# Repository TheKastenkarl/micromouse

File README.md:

# Micromouse: Designing an Educational Racing - Robot from Scratch [TUM IN2106/IN4235]

A practical course at TU Munich to build a micromouse robot from scratch, led by [Dr. Ph.D. Alexander Lenz](https://www.ce.cit.tum.de/air/people/dr-alexander-lenz/). This repository serves as a collection of code and ressources during our group work of SS22. See the official [course description](https://campus.tum.de/tumonline/wbLv.wbShowLVDetail?pStpSpNr=950367380&pSpracheNr=2) for further information.

Content overview:
- `src/`: Source and header files for the programming of a [Microchip dsPIC33FJ64MC804](https://www.microchip.com/en-us/product/dsPIC33FJ64MC804) microcontroller using the [MPLAB X IDE](https://www.microchip.com/en-us/tools-resources/develop/mplab-x-ide) and the [MPLAB XC16 Compiler](https://www.microchip.com/en-us/tools-resources/develop/mplab-xc-compilers).
- `pcb/`: Schematics and board layout designed in [Autodesk Eagle](https://www.autodesk.com/products/eagle/overview?term=1-YEAR&tab=subscription).
- `cad/`: 3D printed CAD parts including sensor and motor mountings.

## PCB

List of external Eagle libraries:

| Name  | Usage |
|-------|-------|
| [microchip-dspic33fjxxmc](http://eagle.autodesk.com/eagle/libraries?utf8=%E2%9C%93&q%5Btitle_or_author_or_description_cont%5D=dsPIC33FJ64MC&button=) | Microcontroller DSPIC33FJ64MC804 |
| [Eagle_WCAP-ATG5 (rev21a).lbr](https://www.we-online.com/catalog/en/DESIGNKIT_860022) | Electrolytic Capacitors |
| [Eagle_WE-TIS (rev22a).lbr](https://www.we-online.com/catalog/en/WE-TIS) | Inductances |
| [Eagle_WE-XTAL (rev21c).lbr](https://www.we-online.com/catalog/en/WE-XTAL) | Oscillator Quartz Crystal |
| [SamacSys_Parts.lbr](https://github.com/vincent290587/EAGLE/blob/master/SamacSys/SamacSys_Parts.lbr) | Power Switch |
 
## Instructions for high-level maze solver
### 1) Allocate heap memory.
With the microchip compiler you have to allocate heap memory in the project properties ([tutorial from Microchip](https://microchipdeveloper.com/mplabx:creating-a-heap)). Use for example 4096 bytes.
### 2) If necesarry, adapt the settings of the high-level maze solver in `src/settings.h`.
- MAZE_SIZE: Number of columns (= number of rows) of maze.
- SIMULATION: Defines if simulation or real robot is used (used simulation: [mms by mackorone](https://github.com/mackorone/mms)).
- VISUALIZATION: Defines if in simulation visualization should be used.
### 3) Only if you use the simulation: Rename main files.
Rename `main.c` to `main_not_used.c` (or any other name) and rename `main_simulation.c` to `main.c`.
### 4) Start high-level maze solver.
- For simulation: Compile code and then follow the instructions of [mms by mackorone](https://github.com/mackorone/mms).
- For real-world Micromouse: Flash the compiled code onto the Micromouse robot and put the Micromouse into the starting position (bottom left corner of the maze, i.e. you have to place the mouse in one of the corners such that there is an outer wall of the maze on the left side of the mouse). Then turn the Micromouse on. After 10 seconds, it will automatically start exploring. After the exploration phase, it calculates and executes the shortest path from the starting cell to the center of the maze.

## Some impressions
Finished Micromouse: <br/>
 <br/>

6 x 6 maze to test the Micromouse: <br/>
 <br/>

Testing the high-level maze solver in simulation: <br/>
 <br/>

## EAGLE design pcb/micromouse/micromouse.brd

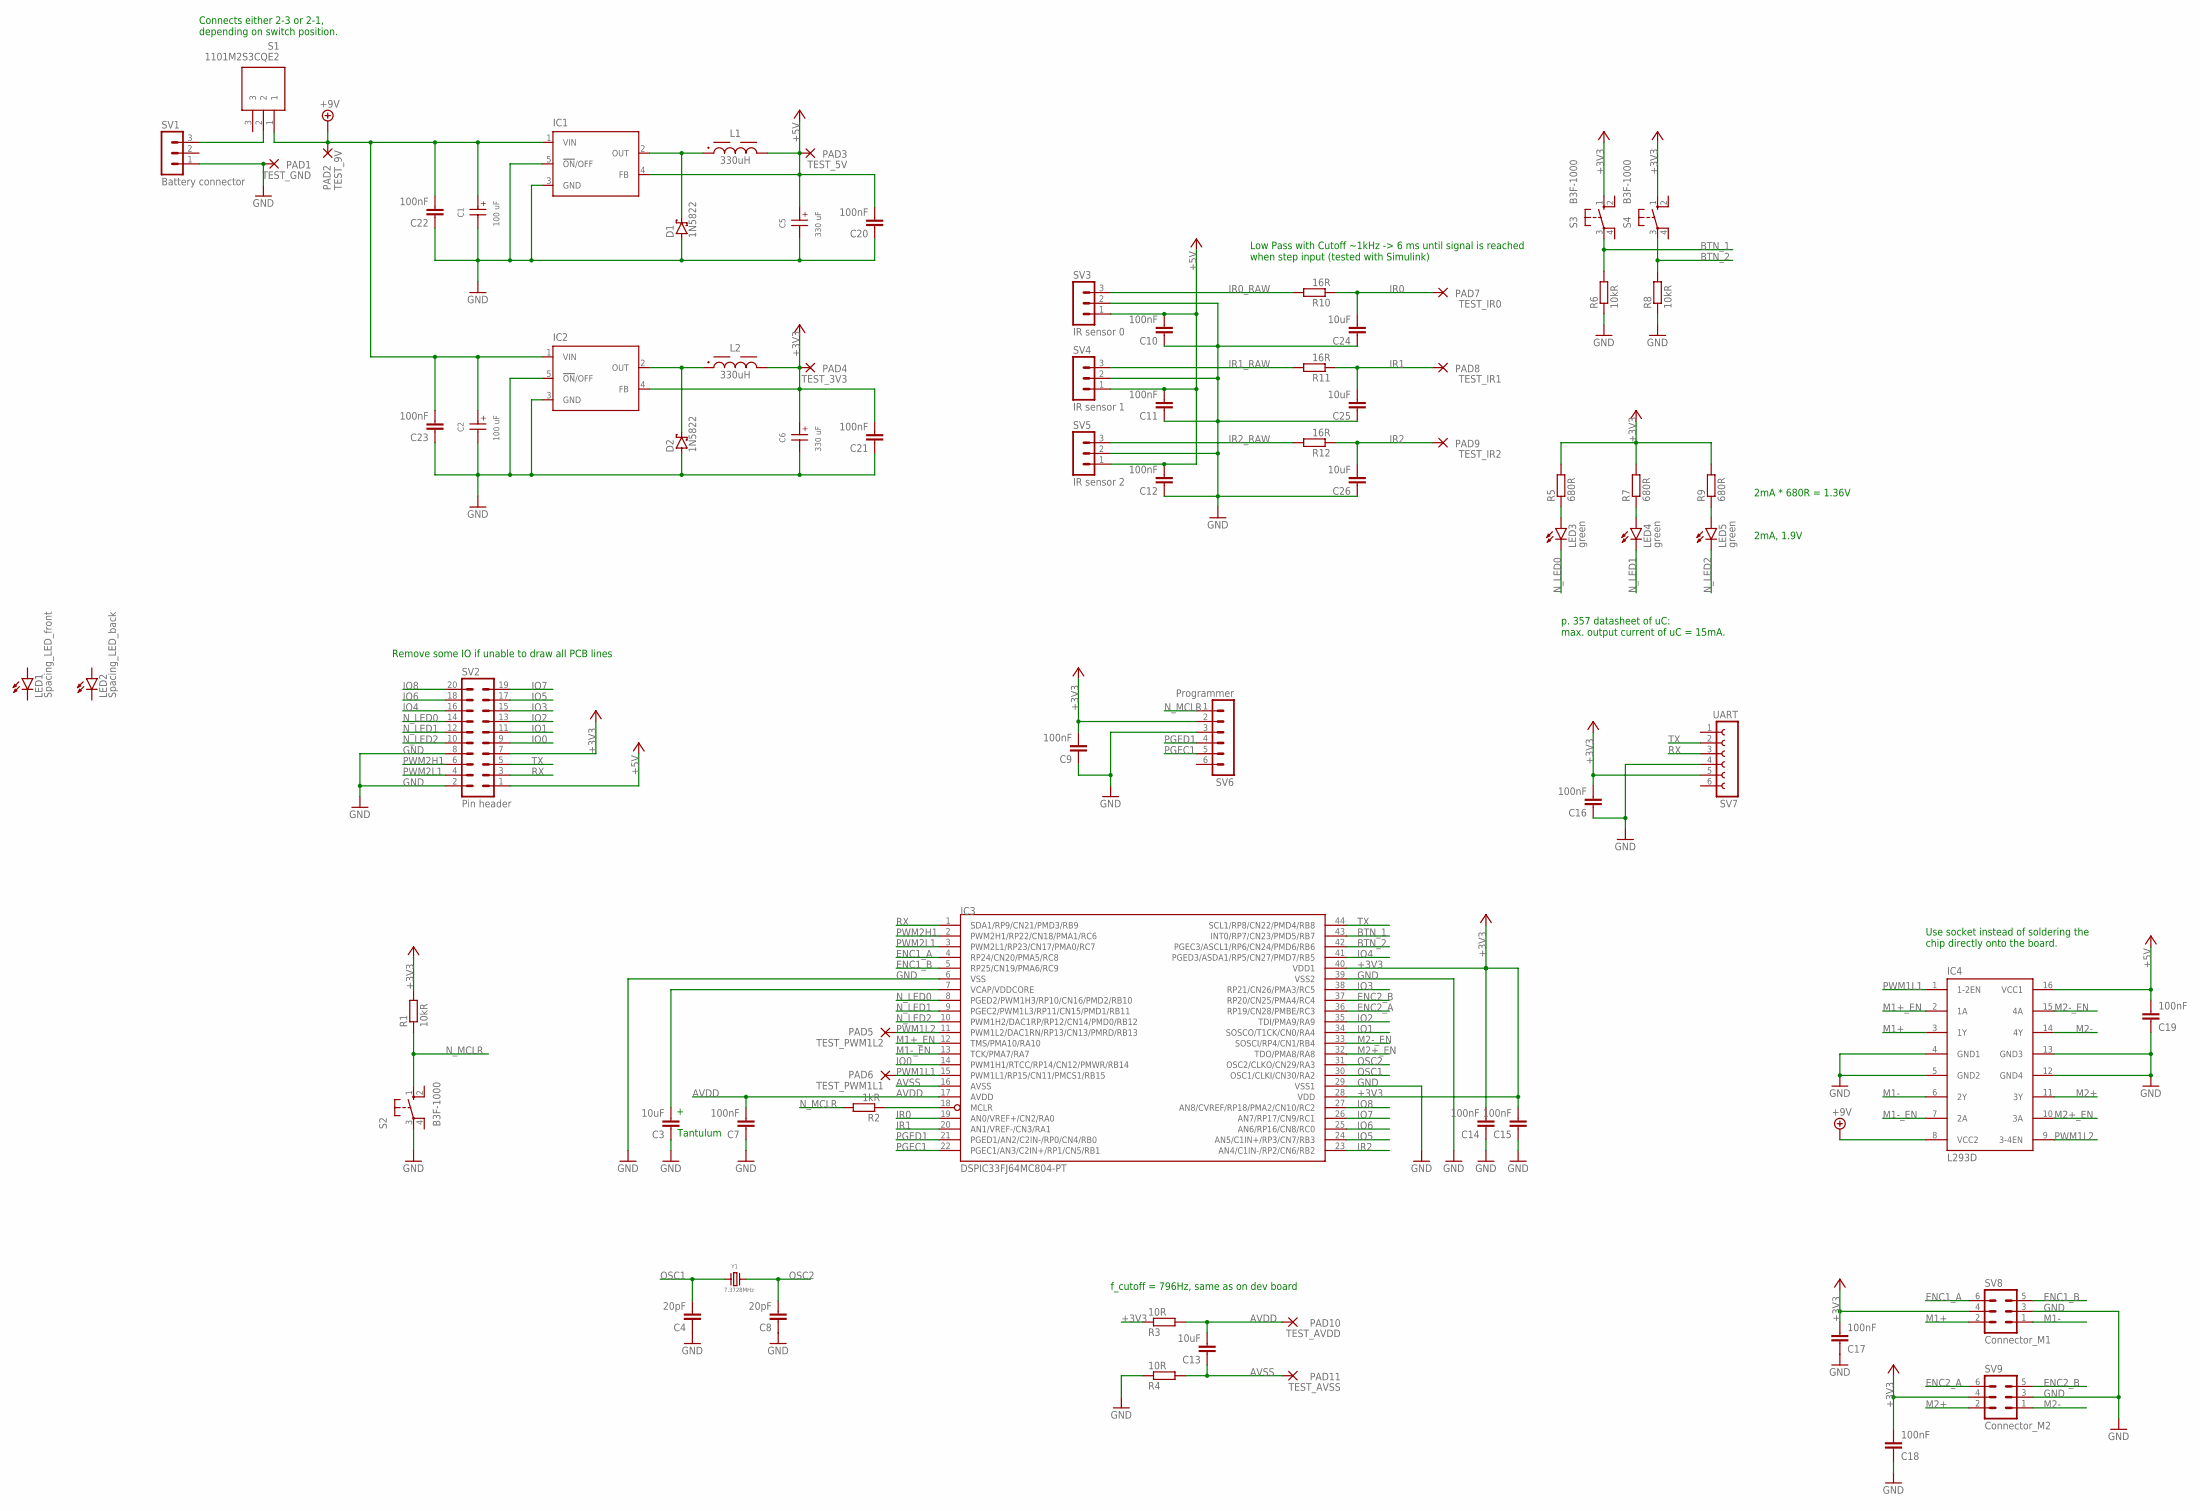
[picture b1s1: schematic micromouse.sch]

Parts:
C1, C2: 100 uF; WCAP-ATG5_5X11(DXL)
C3, C13, C24, C25, C26: 10uF; C0805
C4, C8: 20pF; C0805
C5, C6: 330 uF; WCAP-ATG5_6.3X11(DXL)
C7, C9, C10, C11, C12, C14, C15, C16, C17, C18, C19, C20, C21, C22, C23: 100nF; C0805
D1, D2: 1N5822; DO35-10
IC1: LM2575-5.0WU-(TR); TO263-5
IC2: LM2575-3.3WU-(TR); TO263-5
IC3: DSPIC33FJ64MC804-PT; TQFP44
IC4: L293D; DIL16
L1, L2: 330uH; WE-TIS_1111
LED1: Spacing_LED_front; LED5MM
LED2: Spacing_LED_back; LED5MM
LED3, LED4, LED5: green; CHIP-LED0805
PAD1: TEST_GND; 3,17/1,3
PAD2: TEST_9V; 3,17/1,3
PAD3: TEST_5V; 3,17/1,3
PAD4: TEST_3V3; 3,17/1,3
PAD5: TEST_PWM1L2; 3,17/1,3
PAD6: TEST_PWM1L1; 3,17/1,3
PAD7: TEST_IR0; 3,17/1,3
PAD8: TEST_IR1; 3,17/1,3
PAD9: TEST_IR2; 3,17/1,3
PAD10: TEST_AVDD; 3,17/1,3
PAD11: TEST_AVSS; 3,17/1,3
R1, R6, R8: 10kR; R0805
R2: 1kR; R0805
R3, R4: 10R; R0805
R5, R7, R9: 680R; R0805
R10, R11, R12: 16R; R0805
S1: 1101M2S3CQE2; 1000-SERIES(SPDT)
S2, S3, S4: B3F-1000; B3F-10XX
SV1: Battery connector; MA03-1
SV2: Pin header; MA10-2
SV3: IR sensor 0; MA03-1
SV4: IR sensor 1; MA03-1
SV5: IR sensor 2; MA03-1
SV6: Programmer; MA06-1
SV7: UART; FE06
SV8: Connector_M1; ML6
SV9: Connector_M2; ML6
Y1: 7.3728MHz; WE-XTAL_HC49/4H

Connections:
+3V3: C6.1 (+), C9.2, C14.2, C15.2, C16.2, C17.2, C18.2, C21.2, IC2.4 (FB), IC3.28 (VDD), IC3.40 (VDD1), L2.2, PAD4.1, R1.2, R3.1, R5.2, R7.2, R9.2, S3.1 (S), S4.1 (S), SV2.7, SV6.2, SV7.5, SV8.4, SV9.4
+5V: C5.1 (+), C10.2, C11.2, C12.2, C19.2, C20.2, IC1.4 (FB), IC4.16 (VCC1), L1.2, PAD3.1, SV2.1, SV3.1, SV4.1, SV5.1
+9V: C1.1 (+), C2.1 (+), C22.2, C23.2, IC1.1 (VIN), IC2.1 (VIN), IC4.8 (VCC2), PAD2.1, S1.1
AVDD: C7.2, C13.2, IC3.17 (AVDD), PAD10.1, R3.2
AVSS: C13.1, IC3.16 (AVSS), PAD11.1, R4.2
BTN_1: IC3.43 (INT0/RP7/CN23/PMD5/RB7), R6.2, S3.3
BTN_2: IC3.42 (PGEC3/ASCL1/RP6/CN24/PMD6/RB6), R8.2, S4.3
ENC1_A: IC3.4 (RP24/CN20/PMA5/RC8), SV8.6
ENC1_B: IC3.5 (RP25/CN19/PMA6/RC9), SV8.5
ENC2_A: IC3.36 (RP19/CN28/PMBE/RC3), SV9.6
ENC2_B: IC3.37 (RP20/CN25/PMA4/RC4), SV9.5
GND: C1.2 (-), C2.2 (-), C3.1, C4.1, C5.2 (-), C6.2 (-), C7.1, C8.1, C9.1, C10.1, C11.1, C12.1, C14.1, C15.1, C16.1, C17.1, C18.1, C19.1, C20.1, C21.1, C22.1, C23.1, C24.1, C25.1, C26.1, D1.A, D2.A, IC1.3 (GND), IC1.5 (!ON!/OFF), IC2.3 (GND), IC2.5 (!ON!/OFF), IC3.6 (VSS), IC3.29 (VSS1), IC3.39 (VSS2), IC4.4 (GND1), IC4.5 (GND2), IC4.12 (GND4), IC4.13 (GND3), PAD1.1, R4.1, R6.1, R8.1, S2.3, SV1.1, SV2.2, SV2.8, SV3.2, SV4.2, SV5.2, SV6.3, SV7.4, SV8.3, SV9.3
IO0: IC3.14 (PWM1H1/RTCC/RP14/CN12/PMWR/RB14), SV2.9
IO1: IC3.34 (SOSCO/T1CK/CN0/RA4), SV2.11
IO2: IC3.35 (TDI/PMA9/RA9), SV2.13
IO3: IC3.38 (RP21/CN26/PMA3/RC5), SV2.15
IO4: IC3.41 (PGED3/ASDA1/RP5/CN27/PMD7/RB5), SV2.16
IO5: IC3.24 (AN5/C1IN+/RP3/CN7/RB3), SV2.17
IO6: IC3.25 (AN6/RP16/CN8/RC0), SV2.18
IO7: IC3.26 (AN7/RP17/CN9/RC1), SV2.19
IO8: IC3.27 (AN8/CVREF/RP18/PMA2/CN10/RC2), SV2.20
IR0: C24.2, IC3.19 (AN0/VREF+/CN2/RA0), PAD7.1, R10.1
IR0_RAW: R10.2, SV3.3
IR1: C25.2, IC3.20 (AN1/VREF-/CN3/RA1), PAD8.1, R11.1
IR1_RAW: R11.2, SV4.3
IR2: C26.2, IC3.23 (AN4/C1IN-/RP2/CN6/RB2), PAD9.1, R12.1
IR2_RAW: R12.2, SV5.3
M1+: IC4.3 (1Y), SV8.2
M1+_EN: IC3.12 (TMS/PMA10/RA10), IC4.2 (1A)
M1-: IC4.6 (2Y), SV8.1
M1-_EN: IC3.13 (TCK/PMA7/RA7), IC4.7 (2A)
M2+: IC4.11 (3Y), SV9.2
M2+_EN: IC3.32 (TDO/PMA8/RA8), IC4.10 (3A)
M2-: IC4.14 (4Y), SV9.1
M2-_EN: IC3.33 (SOSCI/RP4/CN1/RB4), IC4.15 (4A)
unnamed: IC3.18 (MCLR), R2.1
unnamed: S1.2, SV1.3
unnamed: LED3.A, R5.1
unnamed: LED4.A, R7.1
unnamed: LED5.A, R9.1
unnamed: D1.C, IC1.2 (OUT), L1.1
unnamed: D2.C, IC2.2 (OUT), L2.1
N_LED0: IC3.8 (PGED2/PWM1H3/RP10/CN16/PMD2/RB10), LED3.C, SV2.14
N_LED1: IC3.9 (PGEC2/PWM1L3/RP11/CN15/PMD1/RB11), LED4.C, SV2.12
N_LED2: IC3.10 (PWM1H2/DAC1RP/RP12/CN14/PMD0/RB12), LED5.C, SV2.10
N_MCLR: R1.1, R2.2, S2.1 (S), SV6.1
OSC1: C4.2, IC3.30 (OSC1/CLKI/CN30/RA2), Y1.1
OSC2: C8.2, IC3.31 (OSC2/CLKO/CN29/RA3), Y1.2
PGEC1: IC3.22 (PGEC1/AN3/C2IN+/RP1/CN5/RB1), SV6.5
PGED1: IC3.21 (PGED1/AN2/C2IN-/RP0/CN4/RB0), SV6.4
PWM1L1: IC3.15 (PWM1L1/RP15/CN11/PMCS1/RB15), IC4.1 (1-2EN), PAD6.1
PWM1L2: IC3.11 (PWM1L2/DAC1RN/RP13/CN13/PMRD/RB13), IC4.9 (3-4EN), PAD5.1
PWM2H1: IC3.2 (PWM2H1/RP22/CN18/PMA1/RC6), SV2.6
PWM2L1: IC3.3 (PWM2L1/RP23/CN17/PMA0/RC7), SV2.4
RX: IC3.1 (SDA1/RP9/CN21/PMD3/RB9), SV2.3, SV7.3
TX: IC3.44 (SCL1/RP8/CN22/PMD4/RB8), SV2.5, SV7.2
VCAP/VDDCORE: C3.2, IC3.7 (VCAP/VDDCORE)

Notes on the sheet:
p. 357 datasheet of uC: max. output current of uC = 15mA.
2mA, 1.9V
2mA * 680R = 1.36V
Use socket instead of soldering the chip directly onto the board.
f_cutoff = 796Hz, same as on dev board
Connects either 2-3 or 2-1, depending on switch position.
Remove some IO if unable to draw all PCB lines
Tantulum
Low Pass with Cutoff ~1kHz -> 6 ms until signal is reached when step input (tested with Simulink)

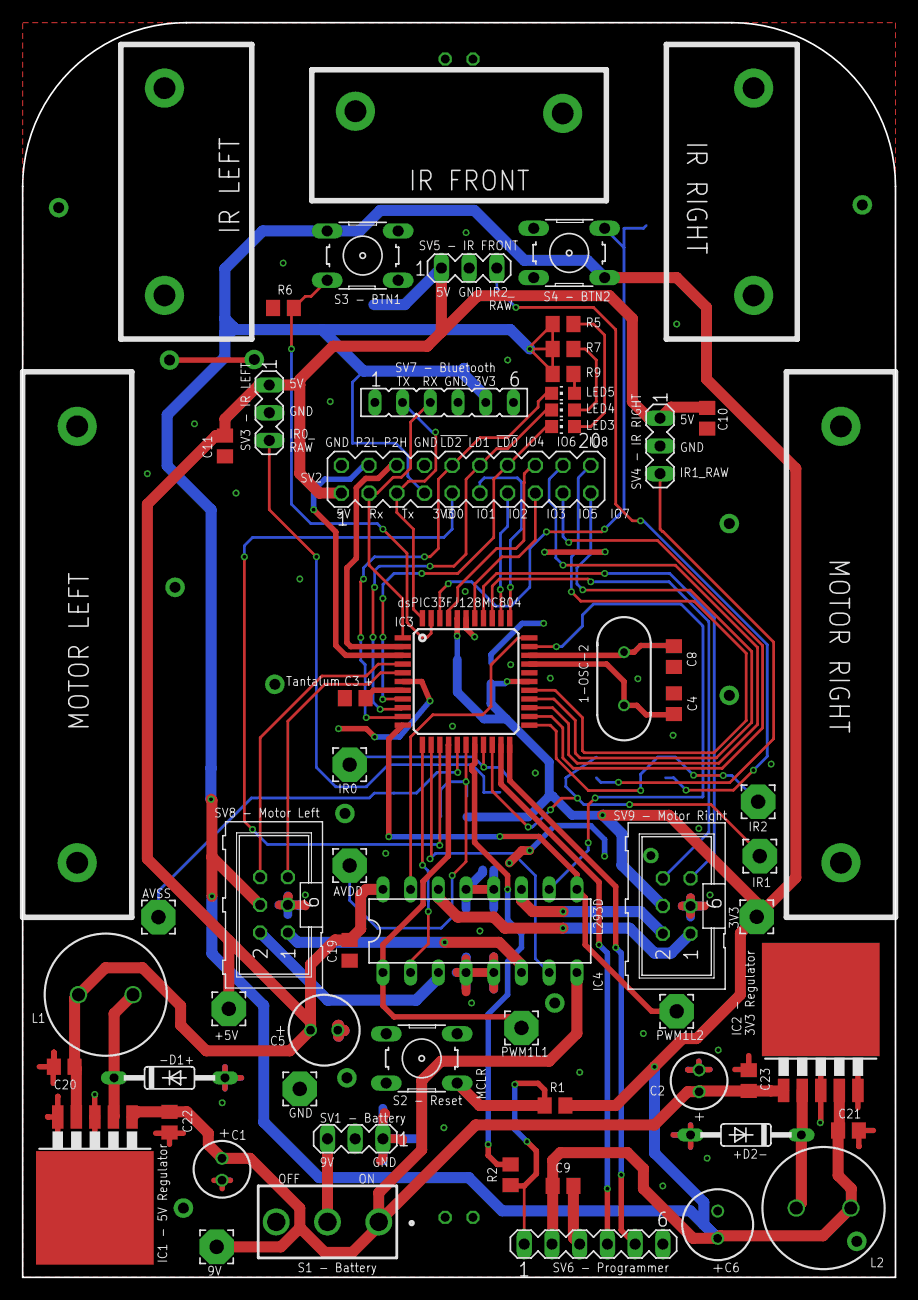
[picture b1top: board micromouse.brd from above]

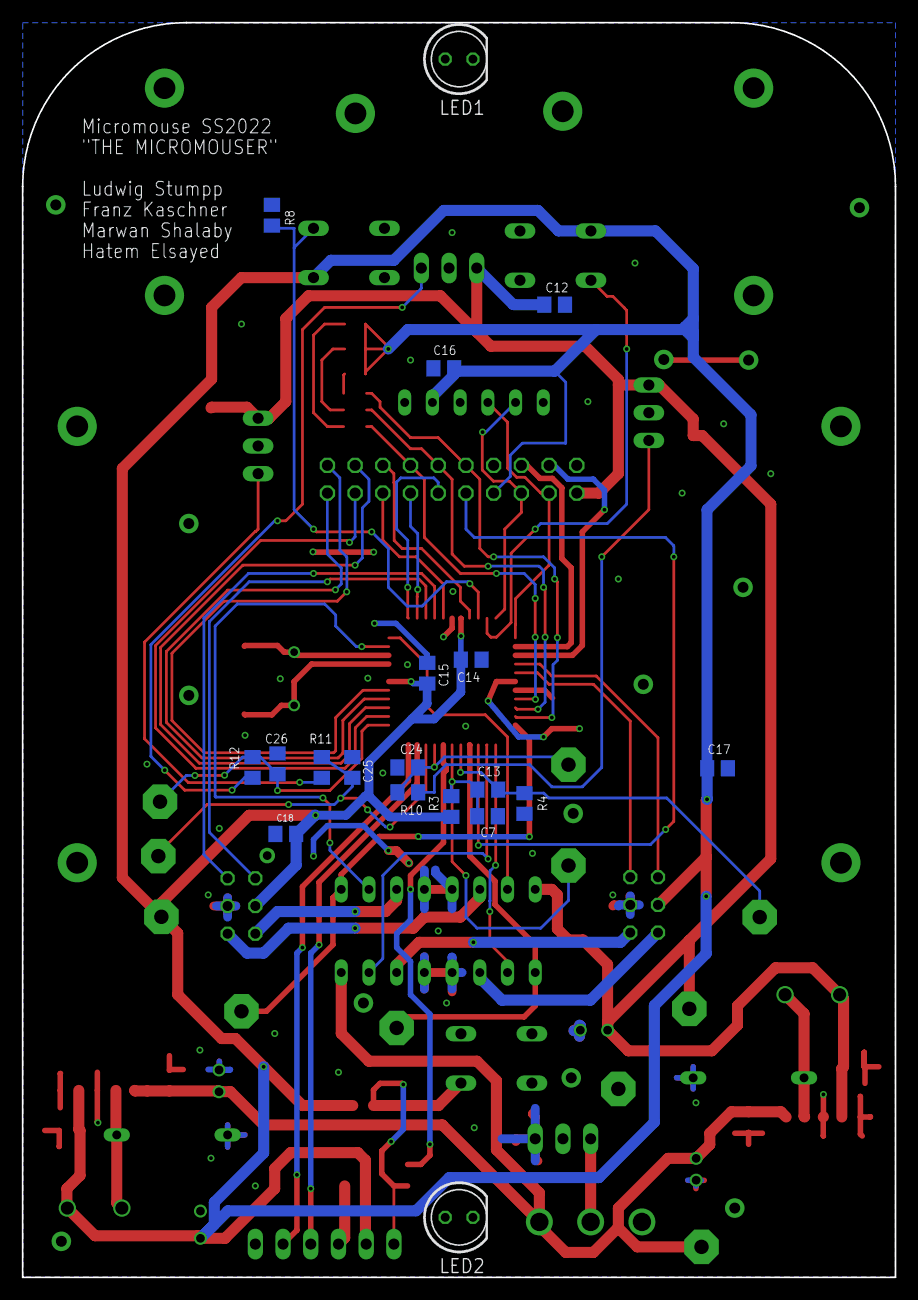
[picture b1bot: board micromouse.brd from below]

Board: 2 copper layers, 80.0 x 115.0 mm, 76 parts (19 on the bottom side), 57 nets.

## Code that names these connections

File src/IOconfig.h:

#ifndef IOCONFIG_H
#define	IOCONFIG_H

/// OUTPUTS 

// use latch for writing to outputs, pin numbers from board description
#define LED0 LATBbits.LATB10
#define LED1 LATBbits.LATB11
#define LED2 LATBbits.LATB12
#define M1_PLUS_EN LATAbits.LATA10
#define M1_MINUS_EN LATAbits.LATA7
#define M2_PLUS_EN LATAbits.LATA8
#define M2_MINUS_EN LATBbits.LATB4

// directly define constants for tristate to not forget them
#define LED0_TRIS TRISBbits.TRISB10
#define LED1_TRIS TRISBbits.TRISB11
#define LED2_TRIS TRISBbits.TRISB12
#define M1_PLUS_EN_TRIS TRISAbits.TRISA10
#define M1_MINUS_EN_TRIS TRISAbits.TRISA7
#define M2_PLUS_EN_TRIS TRISAbits.TRISA8
#define M2_MINUS_EN_TRIS TRISBbits.TRISB4

// motors pwm duty cycles
#define M1_DC P1DC1 // PWM1L1, PWM1H1
#define M2_DC P1DC2 // PWM1L2, PWM1H2

/// INPUTS

// use port for reading from inputs
#define BTN1 PORTBbits.RB7 
#define BTN2 PORTBbits.RB6

/// VALUES

// since active low LED
#define LEDON 0
#define LEDOFF 1

// buttons
#define BTN_PRESSED 1

void setupIO();

#endif	/* IOCONFIG_H */

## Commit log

2022-06-08 Initial commit, repo setup
2022-06-08 Fix typo in README
2022-06-13 Started eagle sketch
2022-06-14 Add distance sensors, LEDs and prepared supply
2022-06-14 Add list of used eagle libs to readme
2022-06-15 Added folders for libraries and design rules
2022-06-15 Added design rule from manufacturer
2022-06-15 Schematic: Replace RCL components with european versions, add oscillator and add parts of H bridge.
2022-06-16 Replaced reset switch, added voltage regulators
2022-06-18 Add motor connectors, complete h bridge, add UART pins, add pin header for debugging, change series resistors of LEDs.
2022-06-18 Additional buttons, draft of LED transistor, power switch, few corrections and additional questions
2022-06-18 Fix hluetooth module supply voltage to 3.3V
2022-06-19 Started with hardware parts alignment, add battery holes connection, additional comments
2022-06-19 Add comment regarding connector for distance sensors
2022-06-19 Add correct switch, change connection of LEDs, connect signals from hbridge and motor with uC, fix connection of programmer, add signals to debugging pin header, add front wheel LED, connect capacito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
2022-06-19 Fixed connections of power switch and implemented inductors for voltage regulators
2022-06-20 Add missing junction (two wires were not correctly connected).
2022-06-21 Fix connection of IR sensors
2022-06-21 Additional comment to have coupling capacitor at h bridge
2022-06-21 Additional comment regarding helper header
2022-06-22 first prototyoe for maze solver logic
2022-06-22 initial putting components in place
2022-06-22 Initial commit of mplab project with code for dsPIC33FJ128MC802.
2022-06-22 Change folder structure of source code.
2022-06-22 width: 81mm, height: 99mm curves on front edges All connections done except for ground Not all notes were looked through
2022-06-24 Exchanged 100 uF capacitors at voltage regulator to have 1210 mounting layout + added ground planes
2022-06-24 Fix positioning of power switch.
2022-06-24 Remove resolved comments and only use resistors fom E12 series.
2022-06-24 Use pin header as battery connector and change reset botton setup.
2022-06-25 Removed comment at battery connector. We will use a male one on the board
2022-06-25 Exchanged capacitors and inductances in power supply
2022-06-25 Add test points
2022-06-26 Increase width of lanes, all 45 degree angles errors resolved design rules obeyed
2022-06-26 Dimentions corrected
2022-06-26 Holes + Labels
2022-06-26 TO DO notes checked, components not colliding
2022-06-26 Made names more readable
2022-06-26 Renamed parts in ascending order
2022-06-27 Change comment next to series resistors of LEDs (voltage was wrong)
2022-06-28 Wired capacitors, fixed one missing stub error
2022-06-28 Fixed dimensions, mounting, gnd plate
2022-06-28 Fix position of holes for mounts and correct naming of components in silk layer.
2022-06-29 Fix positioning of motor connectors.
2022-06-29 Fixed ground plate isolation distance, mounting holes and errors
2022-06-29 Almost final steps of PCB, before moving the oscillator
2022-06-29 Intermediate state of moving of oscillator
2022-06-29 Finished wiring of oscialltor, few minor improvements and added missing silk labels
2022-06-30 Add group name, move via next to oscillator and replace LEDs with low current LEDs.
2022-06-30 vias+beef gnds
2022-06-30 pcb remarks solve 3V3 branch other side no vias for 9v to H bridge beef gnd pins delete t/b Names make AVDD+AVSS closer better path under uc vias near oscilator, controller and controller voltage reg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
2022-07-01 Change position of silk writings.
2022-07-03 Add 100nF capacitors at inputs and outputs of both switching converters. Add vias for ground stitching.
2022-07-04 Fix minor issues from previous commit.
2022-07-05 Move 100nF capacitors of switching converters close to the input/output of the converters. Connect stitching vias to GND. Activate ground plane (ratsnest).
2022-07-05 Add project folder for MPLAB IDE
2022-07-05 Started with IOconfig and main simplifications
2022-07-05 Improved connection out of 5V regulator in star connection + added one ground via
2022-07-06 Added low pass filter for distance sensors
2022-07-06 Remove extra GND connections or make them smaller. Remove typos. Make enough space for bluetooth module (9mm).
2022-07-06 cosmetics
2022-07-06 Adapting low level code base
2022-07-06 Move front IR sensor more to the center and fixthe positioning of silk writing.
2022-07-06 Fix positioning of silk writing.
2022-07-06 Fixed one ground line and one silk name
2022-07-06 Move 3V3 signal more to the right away from programmer
2022-07-12 Adapted serial communication code + resolved few errors such that now buildable
2022-07-12 Simplified ADC scan setup by inverting the analogue pin setup from the IOConfig
2022-07-12 Added motor functions
2022-07-12 Prepare everything for the test tomorrow
2022-07-12 Updates on Constants for motor encoder
2022-07-12 Add function to measure motor rotation in rotations per sample + add to measurement for tomorrow
2022-07-13 Add config for development board test setup
2022-07-13 Added separate settings header file to later put all settings in there
2022-07-13 Cleanup main, move tests in separate module
2022-07-13 Tristates as defines to not forget them
2022-07-13 Further simplification
2022-07-13 Fixed encoder test
    Issue was that we were calculating the velocity every 100 ms while we need it every second
2022-07-14 Simplified the encoder interface by combining the update of absolute and delta counts
2022-07-15 Fixed a few bugs
2022-07-22 First version of working maze solver (exploration: dfs, exploitation: bfs).
2022-07-23 Improve maze solver code and add more commnents.
2022-07-23 Add move_to_cell function, improve visualization and delete old maze solver.
2022-07-23 Move maze solver code to src folder and check that compiling with microchip compiler works. Main of maze solver is not yet merged with original main.
2022-08-02 Added code for reading and testing IR values
2022-08-02 Helper function to calculate BRD value for baudrate
2022-08-07 Add function to test buttons and leds
2022-08-08 Few fixes + first working version on our mouse
2022-08-08 Cosmetics and comments
2022-08-11 All tests succesful
2022-08-11 Improved motor test
2022-08-23 Added exp. moving average filter for IR values
2022-08-23 Removed not needed imports
2022-08-24 Added comment for IR functions
2022-08-24 Changed baudrate from 9600 to 57600
2022-08-24 Added optional sleep in main
2022-08-25 Removed pcb library that was not in use
2022-08-25 Fixed external eagle library listings
2022-08-26 control rebase
2022-08-26 gain changes plus test code
2022-09-01 implement bridge fncs
2022-09-18 controller changes, bridge fncs and tuning
2022-09-18 change fnc return type
2022-09-19 Fix high-level path planner (move_to_cell did not work correctly when starting at cell 0)
2022-09-19 Prepare high-level code for real robot.
2022-09-21 gain tuning
2022-09-22 Testing the mouse with hard coded commands
2022-09-23 remove tests in timer.c
2022-09-23 cleanup
2022-09-23 Add UART outputs to high-level maze solver.
2022-09-23 Add UART outputs to high-level maze solver, part 2.
2022-09-23 Add delay to main function to have time to connect UART.
2022-09-23 Add UART outputs to high-level maze solver, part 3. Increase distance of move forward.
2022-09-23 Add UART outputs to high-level maze solver, part 4.
2022-09-23 Remove most of the UART outputs and add function to output wall positions of stored maze via UART.
2022-09-23 Remove most of the UART outputs and add function to output wall positions of stored maze via UART, part 2.
2022-09-23 Adapt function to output wall positions of stored maze. Now it also works in simulation.
2022-09-24 Move function for outputting the maze to maze.h.
2022-11-03 Add instructions for high-level maze solver to readme file.
2022-11-09 disable SIM
2023-02-19 Update readme with impressions

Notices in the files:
parts and their libraries:
Eagle_WE-XTAL: Copyright: Würth Elektronik
